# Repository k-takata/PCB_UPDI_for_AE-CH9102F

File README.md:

# UPDI Adapter for AE-CH9102F (Rev. 3)

## 概要

[秋月電子](https://akizukidenshi.com/)の[CH9102F USBシリアル変換モジュールキット Type-C (AE-CH9102F-TYPEC-BO)](https://akizukidenshi.com/catalog/g/g129505/)を、AVRマイコンのUPDI (Unified Program and Debug Interface)書き込み装置として使うためのアダプターです。

UPDI書き込みモードとシリアル通信モードは自動的に切り替わります。(Rev. 2以降)

UPDI部分の回路は[SerialUPDI](https://github.com/SpenceKonde/AVR-Guidance/blob/master/UPDI/jtag2updi.md)の "No resistor on target OR adapter" の回路を元に、RTS信号による自動切り替え機能を追加してあります。

注: 本アダプターは高電圧(HV)プログラミングには対応していません。HVプログラミングが必要な場合は、関連プロジェクトの[UPDI Unbricker](https://github.com/k-takata/PCB_updi_unbricker)を参照してください。

## 使用したソフトウェア

KiCad 9.0

## 回路図

Rev. 3  

## 基板パターン図

Rev. 3  

## 部品表

| Reference |個数|値    | 説明 |
|-----------|----|------|------|
|D1         |   1|[BAT43XV2](https://akizukidenshi.com/catalog/g/g106467/)|SOD-523、適当なショットキーバリアダイオード|
|J1         |   1|      |L型ピンソケット 2x4 (\*1)、AE-CH9102F-TYPEC-BO接続用 |
|J2         |   1|      |ピンソケット 1x4、UPDI接続用|
|J3         |   1|      |[L型ピンソケット 1x6](https://akizukidenshi.com/catalog/g/g109862/)、TTL Serial接続用|
|J4         |   1|      |ピンヘッダー 1x3、RTS/DTR切り替え用|
|R1         |   1|470Ω |1608M|
|R2         |   1|100kΩ|1608M|
|SW1        |   1|[SS-12D00G3](https://akizukidenshi.com/catalog/g/g115707/)|スライドスイッチ 1回路2接点 基板用|
|U1         |   1|74LVC1G3157|SOT-23-6、SPDTアナログスイッチ|

(\*1) 例えば、[L型ピンソケット 2x6](https://akizukidenshi.com/catalog/g/g116795/) (1個分)や[L型ピンソケット 2x15](https://akizukidenshi.com/catalog/g/g113419/) (3個分)などを加工して使用する。  

## 使用方法

J1をAE-CH9102F-TYPEC-BOと接続します。AE-CH9102F-TYPEC-BOには付属のピンヘッダーではなく、L型ピンヘッダー 2x4を基板表面側に取り付けておきます。

J2は、[AVR Programming Adapter](https://www.microchip.com/en-us/development-tool/AC31S18A)と同じUPDI v2コネクターとなっています。
ただし、1番ピンのRESETは未接続です。(高電圧プログラミングには対応していません。)

| Pin | 機能       | 色 |
|-----|------------|----|
|   1 | RESET (NC) | 白 |
|   2 | VDD (5V)   | 赤 |
|   3 | GND        | 黒 |
|   4 | UPDI       | 緑 |

J3は、一般的な6pinのTTLシリアルコネクターとなっています。6番ピンはJ4にジャンパーピンを挿すことでRTSかDTRのどちらかを選択できます。

| Pin | 機能       | 色 |
|-----|------------|----|
|   1 | GND        | 黒 |
|   2 | CTS        | 茶 |
|   3 | VDD (5V)   | 赤 |
|   4 | TxD        | 橙 |
|   5 | RxD        | 黄 |
|   6 | RTS / DTR  | 緑 |

SW1は、本アダプターから5Vを供給するかどうかを選択します。シルクのONの側に倒すと5Vを供給し、OFFの側に倒すと供給しません。マイコンに対して別の経路で電源を供給済みの場合はOFFにしてください。

UPDI書き込みモードとシリアル通信モードは自動的に切り替わります。
RTSがアクティブ(Low)の場合、シリアル通信モードとなり、そうでなければUPDIモードとなります。

Rev. 1では切り替え回路を単純にするため、2回路2接点スイッチではなく、1回路2接点スイッチを使用し、TxD側は接続したままとし、RxD側のみ（つまりAVRから送信する側）を切り替えるようにしていました。  
Rev. 2ではそれを発展させ、Nch MOSFET, Pch MOSFET, ショットキー・ダイオード（と追加のプルアップ抵抗）のみで自動切り替えを実現していました。 (先行事例としては、4052/4053などのアナログスイッチICで2回路2接点スイッチを構成する例が多いようです。)  
Rev. 1ではUPDIデータ線はRxDと直結していましたが、Rev. 2ではQ1を介すように変更しています。Rev. 1の接続では、シリアル通信モードでAVRから送信したデータがUPDIにも届くため、通信内容によっては誤動作の可能性がありました。

Rev. 3ではディスクリートによるスイッチを74LVC1G3157に変更しています。  

## 変更差分

### Rev. 3

Rev. 3での変更点は以下の通りです。

* ディスクリートによるスイッチを74LVC1G3157に変更。
* 部品を表面実装部品に変更。

### Rev. 2

Rev. 2での変更点は以下の通りです。

* スイッチによるUPDIモードとシリアル通信モードの手動切り替えを廃止し、RTS信号による自動切り替え機能を搭載。
* シルクを微調整。

## 完成品

Rev. 1  

Rev. 2  

Rev. 3  

## License

CC0

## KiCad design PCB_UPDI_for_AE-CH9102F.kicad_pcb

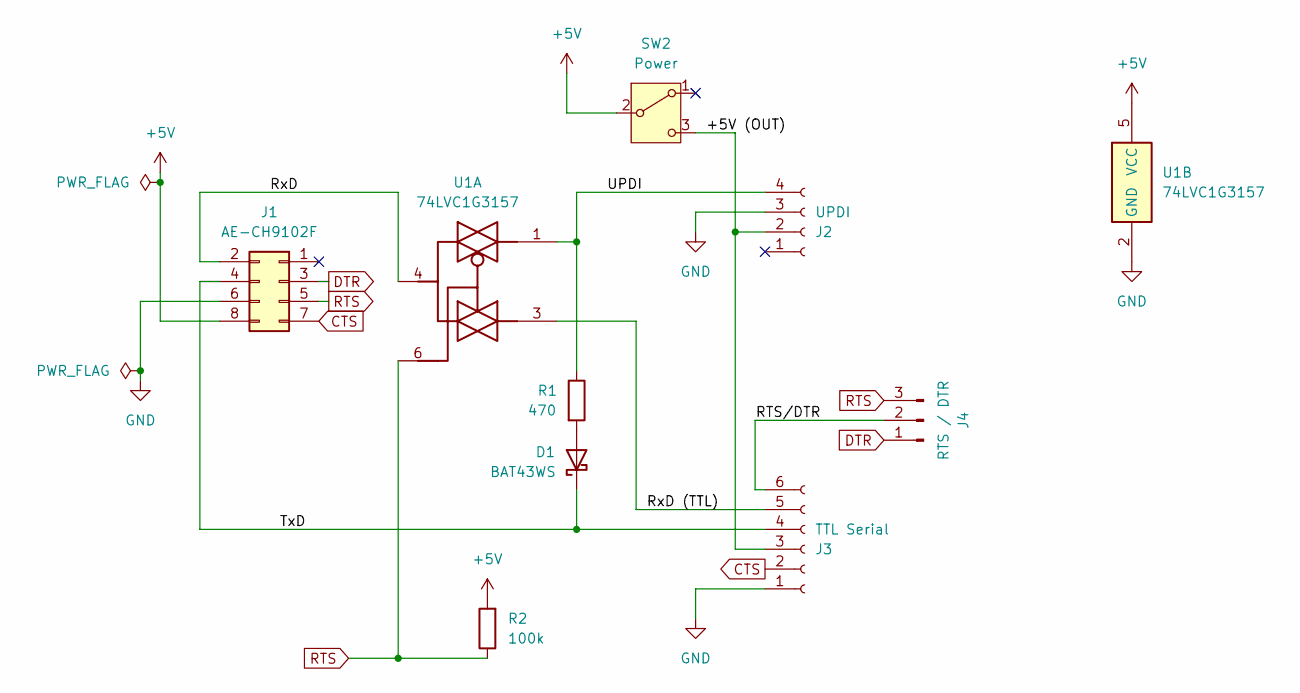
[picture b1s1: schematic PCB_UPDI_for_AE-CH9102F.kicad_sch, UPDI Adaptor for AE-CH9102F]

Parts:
D1: BAT43WS; D_0603_1608Metric
J1: AE-CH9102F; PinSocket_2x04_P2.54mm_Horizontal
J2: UPDI; PinSocket_1x04_P2.54mm_Vertical
J3: TTL Serial; PinSocket_1x06_P2.54mm_Horizontal
J4: RTS / DTR; PinHeader_1x03_P2.54mm_Vertical
R1: 470; R_0603_1608Metric
R2: 100k; R_0603_1608Metric
SW2: Power; PinHeader_1x03_P2.54mm_Vertical
U1: 74LVC1G3157; SOT-23-6

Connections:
+5V: J1.8, R2.2, SW2.2 (B), U1.5 (VCC)
/+5V (OUT): J2.2, J3.3, SW2.3 (C)
/RTS/DTR: J3.6, J4.2
/RxD: J1.2, U1.4
/RxD (TTL): J3.5, U1.3
/TxD: D1.1 (K), J1.4, J3.4
/UPDI: J2.4, R1.1, U1.1
CTS: J1.7, J3.2
DTR: J1.3, J4.1
GND: J1.6, J2.3, J3.1, U1.2 (GND)
unnamed: D1.2 (A), R1.2
RTS: J1.5, J4.3, R2.1, U1.6

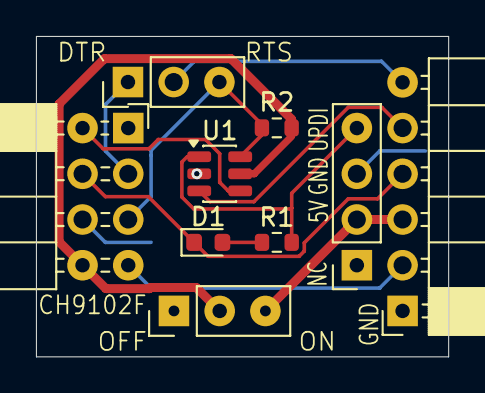
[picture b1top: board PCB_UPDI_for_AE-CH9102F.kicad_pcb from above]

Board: 2 copper layers, 22.9 x 17.8 mm, 9 parts (0 on the bottom side), 12 nets.

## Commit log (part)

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2025-09-22 Initial version
2025-09-22 Add README and images
2025-09-22 Update for fabrication
2025-09-22 Update back silk
2025-10-11 Add picture
2025-11-17 Update J1 connection instructions in README
    Clarify installation instructions for L-shaped pin header.
